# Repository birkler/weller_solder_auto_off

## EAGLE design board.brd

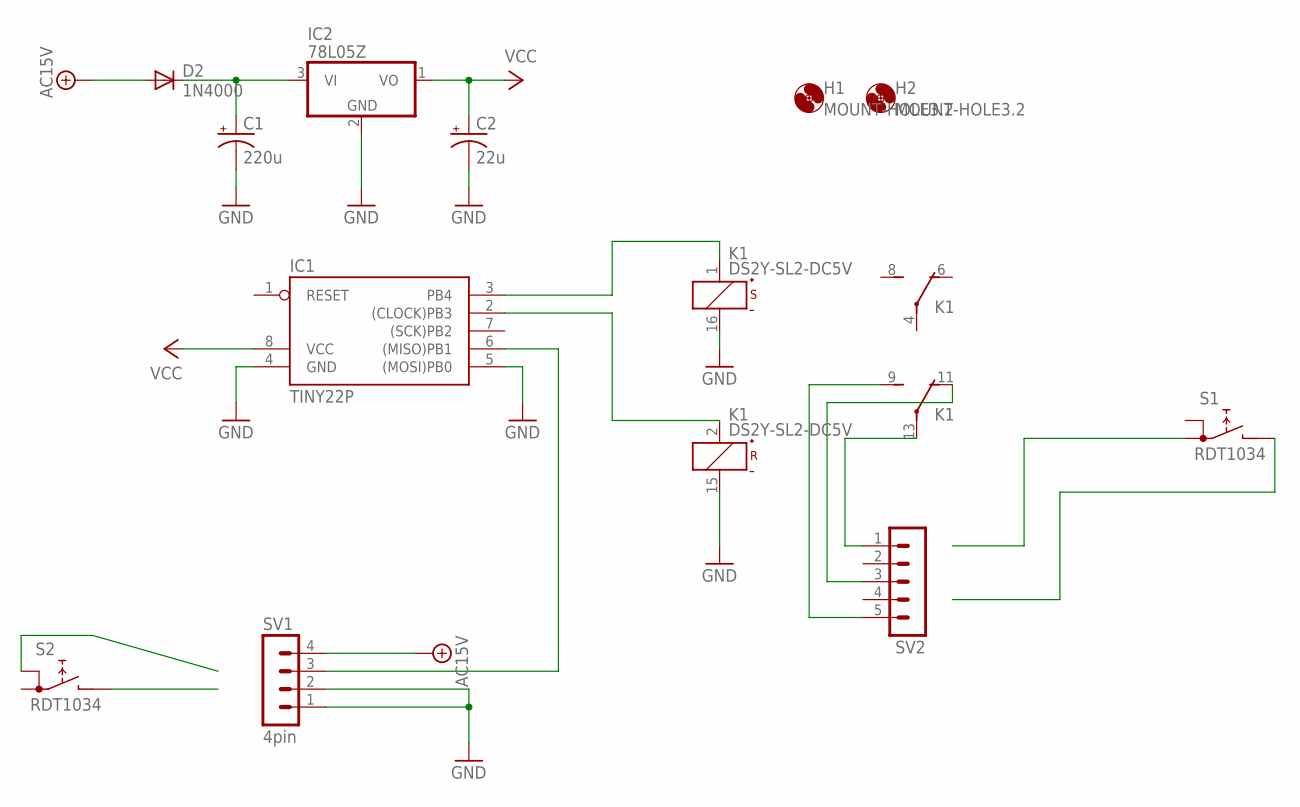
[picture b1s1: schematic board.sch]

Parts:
C1: 220u; E5-10,5
C2: 22u; E5-10,5
D2: 1N4000; D-12.5
H1, H2: MOUNT-HOLE3.2; 3,2
IC1: TINY22P; DIL08
IC2: 78L05Z; TO92
K1: DS2Y-SL2-DC5V; DS2Y-2
S1, S2: RDT1034
SV1: 4pin; MA04-1
SV2: MA05-1

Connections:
+15V: D2.A, SV1.4
GND: C1.-, C2.-, IC1.4 (GND), IC1.5 ((MOSI)PB0), IC2.2 (GND), K1.15 (-), K1.16 (-), SV1.1, SV1.2
unnamed: IC1.3 (PB4), K1.1 (+)
unnamed: IC1.2 ((CLOCK)PB3), K1.2 (+)
unnamed: K1.13, SV2.1
unnamed: K1.9 (S), SV2.5
unnamed: K1.11 (O), SV2.3
unnamed: C1.+, D2.C, IC2.3 (VI)
unnamed: IC1.6 ((MISO)PB1), SV1.3
VCC: C2.+, IC1.8 (VCC), IC2.1 (VO)

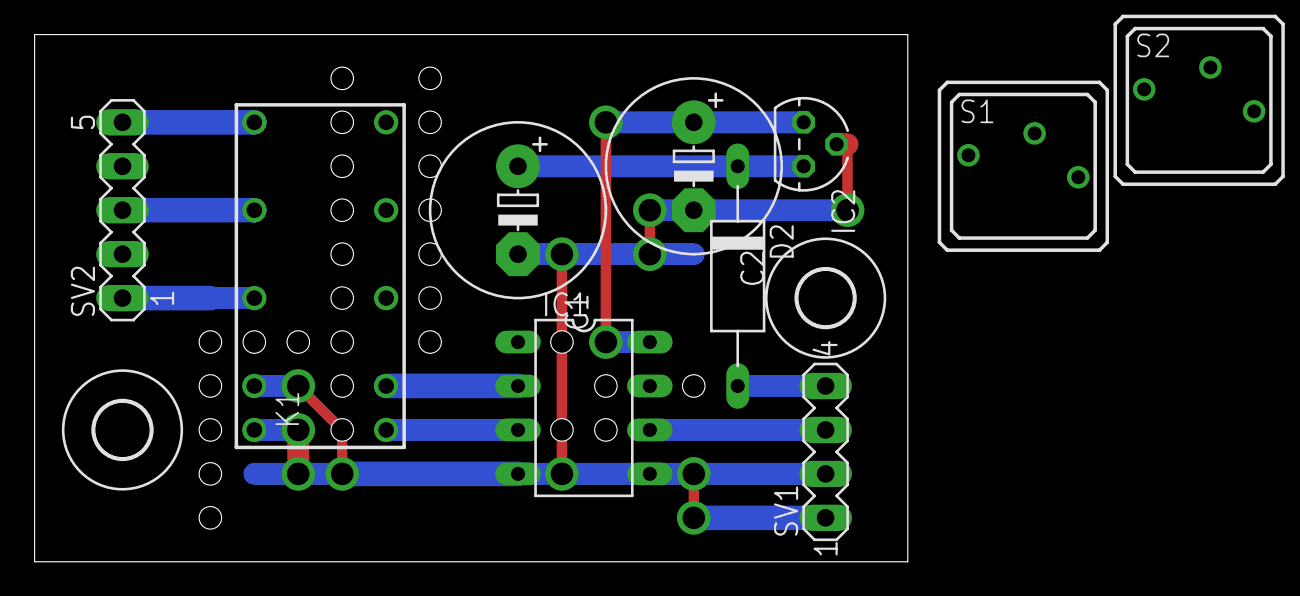
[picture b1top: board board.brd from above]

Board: 2 copper layers, 50.5 x 30.5 mm, 12 parts (0 on the bottom side), 10 nets.

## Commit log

2018-12-11 initial version.
